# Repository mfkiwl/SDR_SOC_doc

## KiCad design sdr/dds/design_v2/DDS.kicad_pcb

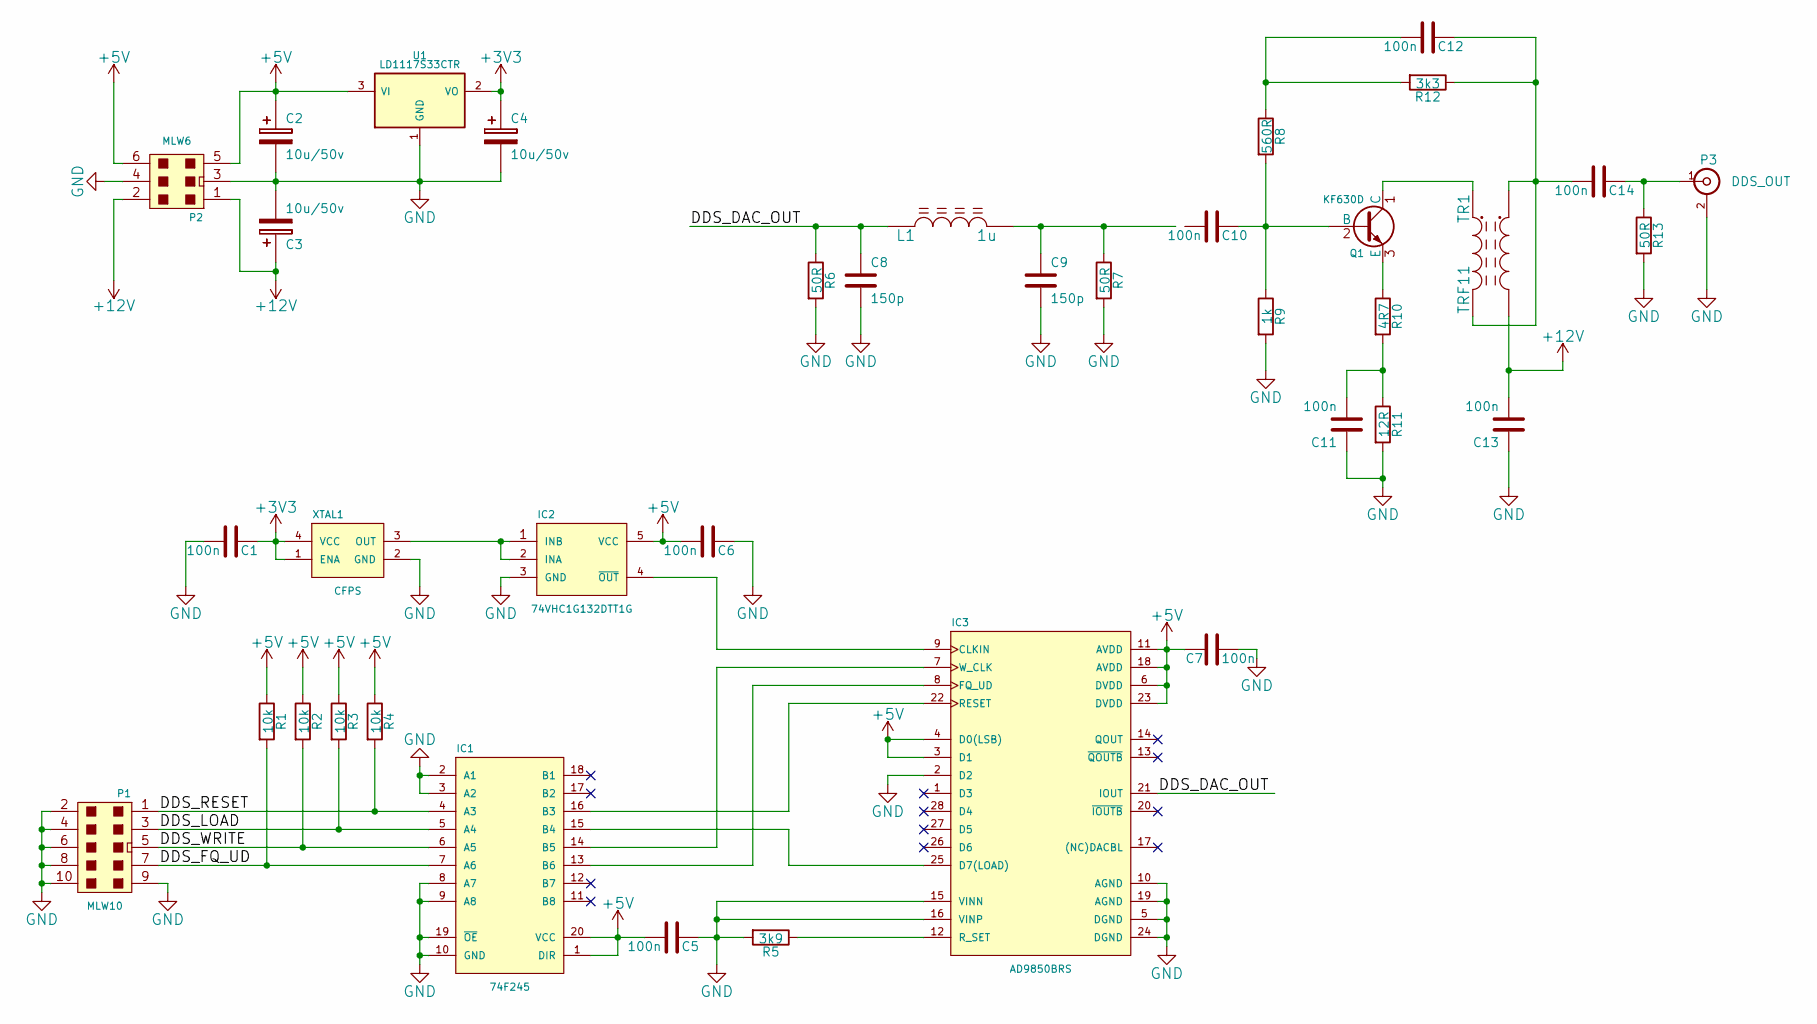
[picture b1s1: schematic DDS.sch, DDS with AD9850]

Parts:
C1, C5, C6, C7, C10, C11, C12, C13, C14: 100n; SMD-0805
C2, C3, C4: 10u/50v; Elko_vert_11.2x6.3mm_RM2.5
C8, C9: 150p; SMD-0805
IC1: 74F245; SO-20-L
IC2: 74VHC1G132DTT1G; SOT-23-5
IC3: AD9850BRS; SSOP-28_5.3x10.2mm_Pitch0.65mm
L1: 1u; R3-LARGE_PADS
P1: MLW10; vasch_strip_5x2_90
P2: MLW6; vasch_strip_3x2_90
P3: DDS_OUT; sma_90_r300.124.403
Q1: KF630D; OldSowjetaera_Transistor_Type-II_BigPads
R1, R2, R3, R4: 10k; R_1206
R5: 3k9; R_1206
R6, R7, R13: 50R; R_1206
R8: 560R; R_1206
R9: 1k; R_1206
R10: 4R7; R_1206
R11: 12R; R_1206
R12: 3k3; R_1206
TR1: TRF11; Transformer_Toroid_horizontal_Diameter12-5mm_Amidon-T44
U1: LD1117S33CTR; SOT-223
XTAL1: CFPS; SMD7x5

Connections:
+3V3: C1.1, C4.1, U1.2 (VO), U1.4, XTAL1.1 (ENA), XTAL1.4 (VCC)
+5V: C2.1, C5.2, C6.2, C7.2, IC1.1 (DIR), IC1.20 (VCC), IC2.5 (VCC), IC3.3 (D1), IC3.4 (D0(LSB)), IC3.6 (DVDD), IC3.11 (AVDD), IC3.18 (AVDD), IC3.23 (DVDD), P2.5, P2.6, R1.1, R2.1, R3.1, R4.1, U1.3 (VI)
+12V: C3.1, C13.2, P2.1, P2.2, TR1.4
/DDS_DAC_OUT: C8.1, IC3.21 (IOUT), L1.1, R6.1
/DDS_FQ_UD: IC1.7 (A6), P1.7, R1.2
/DDS_LOAD: IC1.5 (A4), P1.3, R3.2
/DDS_RESET: IC1.4 (A3), P1.1, R4.2
/DDS_WRITE: IC1.6 (A5), P1.5, R2.2
GND: C1.2, C2.2, C3.2, C4.2, C5.1, C6.1, C7.1, C8.2, C9.2, C11.1, C13.1, IC1.2 (A1), IC1.3 (A2), IC1.8 (A7), IC1.9 (A8), IC1.10 (GND), IC1.19 (~OE), IC2.3 (GND), IC3.2 (D2), IC3.5 (DGND), IC3.10 (AGND), IC3.15 (VINN), IC3.16 (VINP), IC3.19 (AGND), IC3.24 (DGND), P1.2, P1.4, P1.6, P1.8, P1.9, P1.10, P2.3, P2.4, P3.2 (Ext), R5.2, R6.2, R7.2, R9.2, R11.2, R13.2, U1.1 (GND), XTAL1.2 (GND)
unnamed: C10.1, Q1.2 (B), R8.2, R9.1
unnamed: C11.2, R10.2, R11.1
unnamed: C12.1, C14.2, R12.1, TR1.2, TR1.3
unnamed: C12.2, R8.1, R12.2
unnamed: C14.1, P3.1 (In), R13.1
unnamed: IC1.13 (B6), IC3.8 (FQ_UD)
unnamed: IC1.14 (B5), IC3.7 (W_CLK)
unnamed: IC1.15 (B4), IC3.25 (D7(LOAD))
unnamed: IC1.16 (B3), IC3.22 (RESET)
unnamed: IC2.1 (INB), IC2.2 (INA), XTAL1.3 (OUT)
unnamed: IC2.4 (~OUT), IC3.9 (CLKIN)
unnamed: IC3.12 (R_SET), R5.1
unnamed: Q1.1 (C), TR1.1
unnamed: Q1.3 (E), R10.1

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
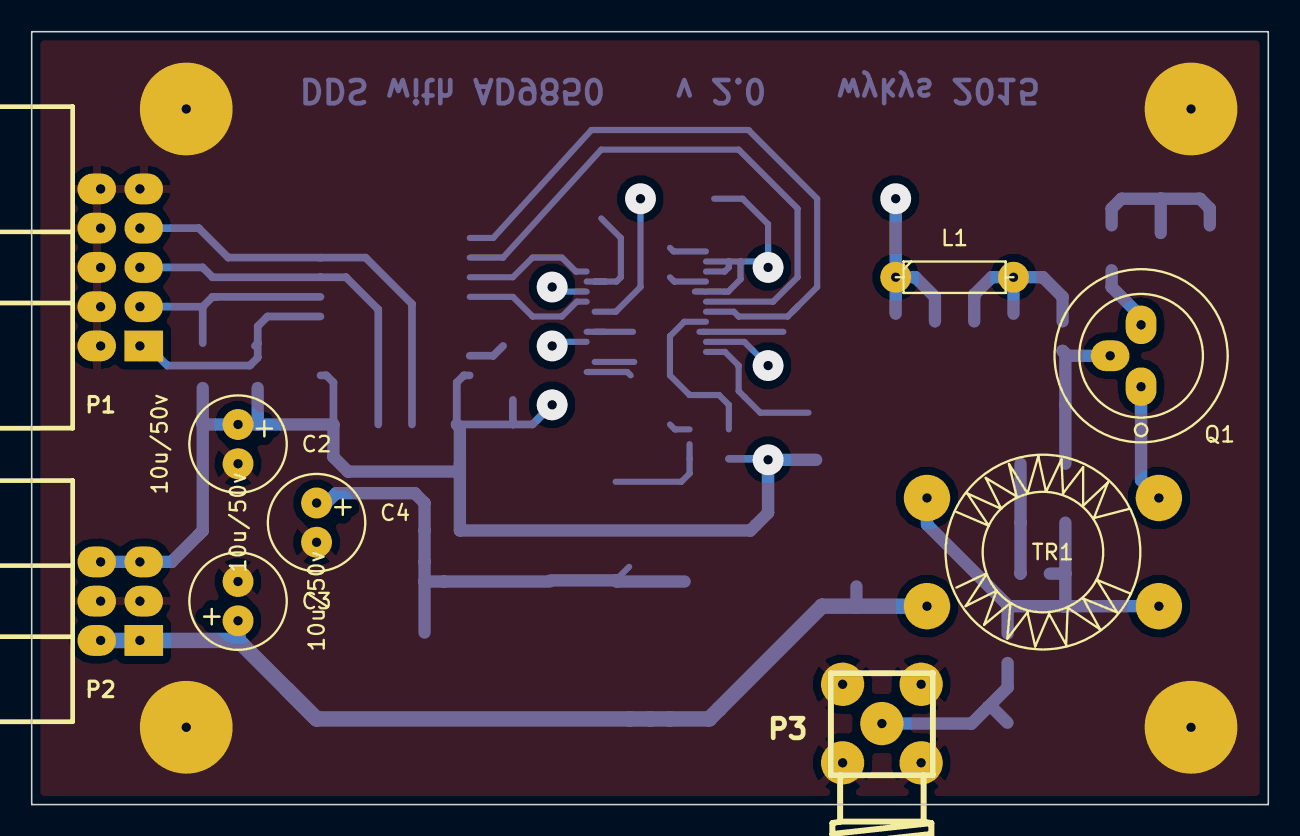
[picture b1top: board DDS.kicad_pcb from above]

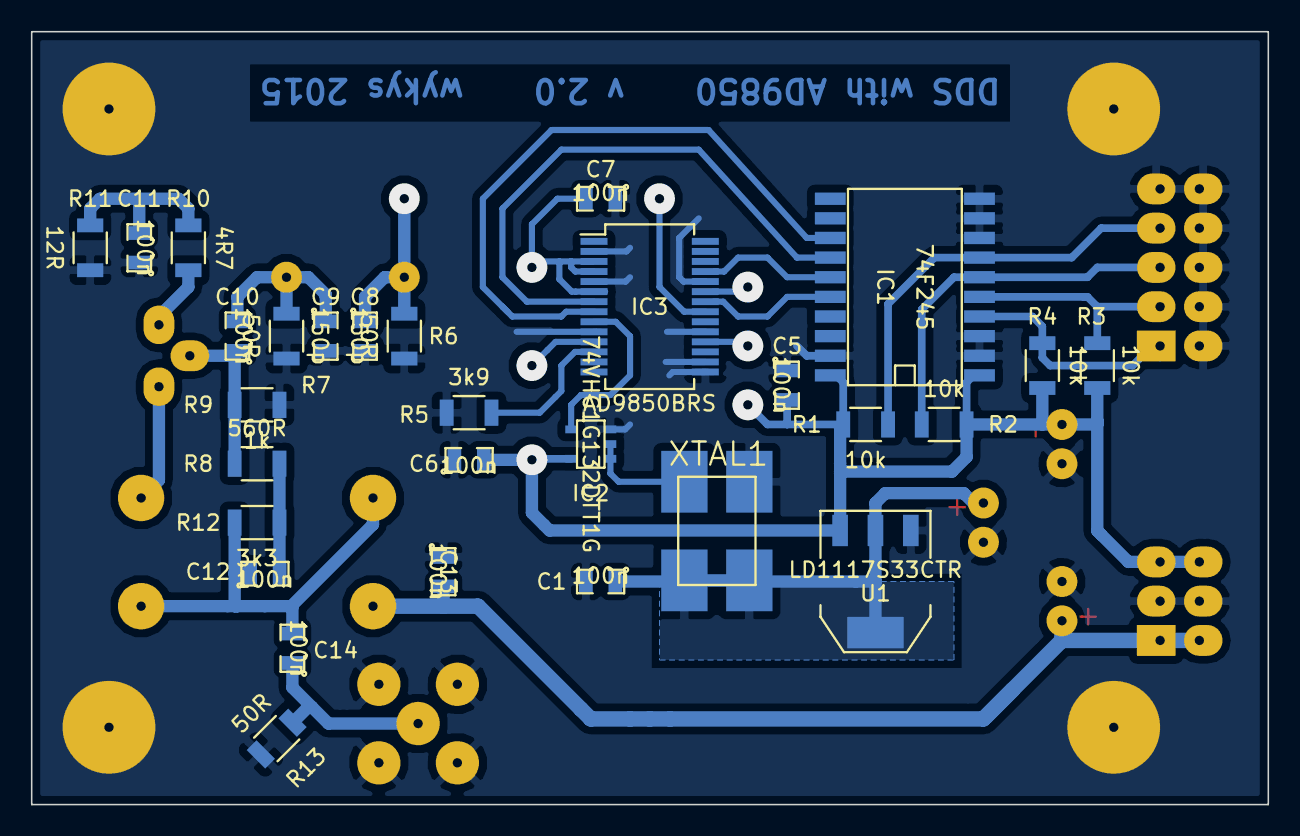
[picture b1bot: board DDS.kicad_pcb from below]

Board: 4 copper layers, 80.0 x 50.0 mm, 38 parts (29 on the bottom side), 24 nets.

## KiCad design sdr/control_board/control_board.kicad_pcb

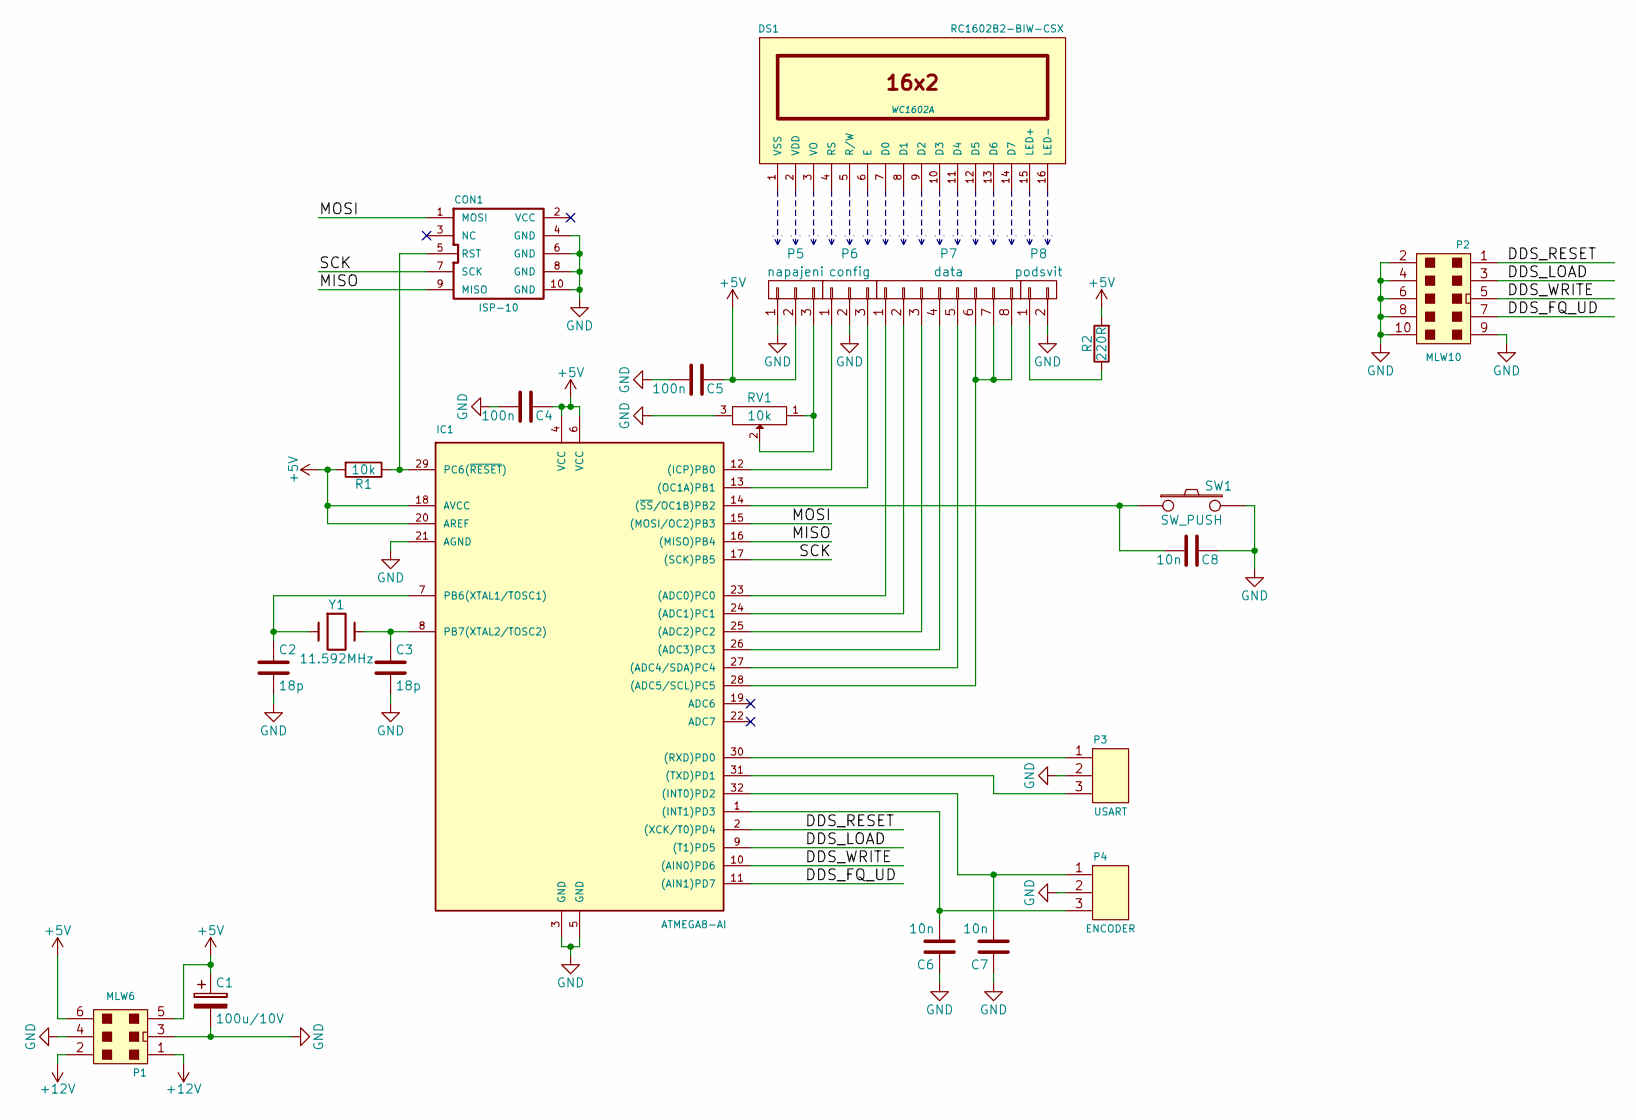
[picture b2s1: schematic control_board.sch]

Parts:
C1: 100u/10V; Elko_vert_11x5mm_RM2.5_CopperClear
C2, C3: 18p; C_0805
C4, C5: 100n; C_0805
C6, C7, C8: 10n; C_0805
CON1: ISP-10; vasch_strip_5x2
DS1: RC1602B2-BIW-CSX; WC1602A
IC1: ATMEGA8-AI; TQFP-32_7x7mm_Pitch0.8mm
P1: MLW6; vasch_strip_3x2_90
P2: MLW10; vasch_strip_5x2_90
P3: USART; MICROSWITCH_SPST
P4: ENCODER; MICROSWITCH_SPST
P5: napajeni; pin_socket_3
P6: config; pin_socket_3
P7: data; pin_socket_8
P8: podsvit; pin_socket_2
R1: 10k; R_1206
R2: 220R; Choke_Horizontal_RM15mm
RV1: 10k; Potentiometer_Trimmer-Suntan-TSR-3386P
SW1: SW_PUSH; Socket_MOLEX-KK-RM2-54mm_Lock_2pin_straight
Y1: 11.592MHz; Crystal_HC49-SD_SMD

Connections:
+5V: C1.1, C4.1, C5.1, IC1.4 (VCC), IC1.6 (VCC), IC1.18 (AVCC), IC1.20 (AREF), P1.5, P1.6, P5.2, R1.2, R2.2
+12V: P1.1, P1.2
/DDS_FQ_UD: IC1.11 ((AIN1)PD7), P2.7
/DDS_LOAD: IC1.9 ((T1)PD5), P2.3
/DDS_RESET: IC1.2 ((XCK/T0)PD4), P2.1
/DDS_WRITE: IC1.10 ((AIN0)PD6), P2.5
/MISO: CON1.9 (MISO), IC1.16 ((MISO)PB4)
/MOSI: CON1.1 (MOSI), IC1.15 ((MOSI/OC2)PB3)
/SCK: CON1.7 (SCK), IC1.17 ((SCK)PB5)
GND: C1.2, C2.2, C3.2, C4.2, C5.2, C6.1, C7.1, C8.1, CON1.4 (GND), CON1.6 (GND), CON1.8 (GND), CON1.10 (GND), IC1.3 (GND), IC1.5 (GND), IC1.21 (AGND), P1.3, P1.4, P2.2, P2.4, P2.6, P2.8, P2.9, P2.10, P3.2, P4.2, P5.1, P6.2, P8.2, RV1.3, SW1.2
unnamed: C2.1, IC1.7 (PB6(XTAL1/TOSC1)), Y1.1
unnamed: C3.1, IC1.8 (PB7(XTAL2/TOSC2)), Y1.2
unnamed: C6.2, IC1.1 ((INT1)PD3), P4.3
unnamed: C7.2, IC1.32 ((INT0)PD2), P4.1
unnamed: C8.2, IC1.14 ((~SS~/OC1B)PB2), SW1.1
unnamed: CON1.5 (RST), IC1.29 (PC6(~RESET~)), R1.1
unnamed: IC1.12 ((ICP)PB0), P6.1
unnamed: IC1.13 ((OC1A)PB1), P6.3
unnamed: IC1.23 ((ADC0)PC0), P7.1
unnamed: IC1.24 ((ADC1)PC1), P7.2
unnamed: IC1.25 ((ADC2)PC2), P7.3
unnamed: IC1.26 ((ADC3)PC3), P7.4
unnamed: IC1.27 ((ADC4/SDA)PC4), P7.5
unnamed: IC1.30 ((RXD)PD0), P3.1
unnamed: IC1.31 ((TXD)PD1), P3.3
unnamed: P5.3, RV1.1, RV1.2
unnamed: P8.1, R2.1

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
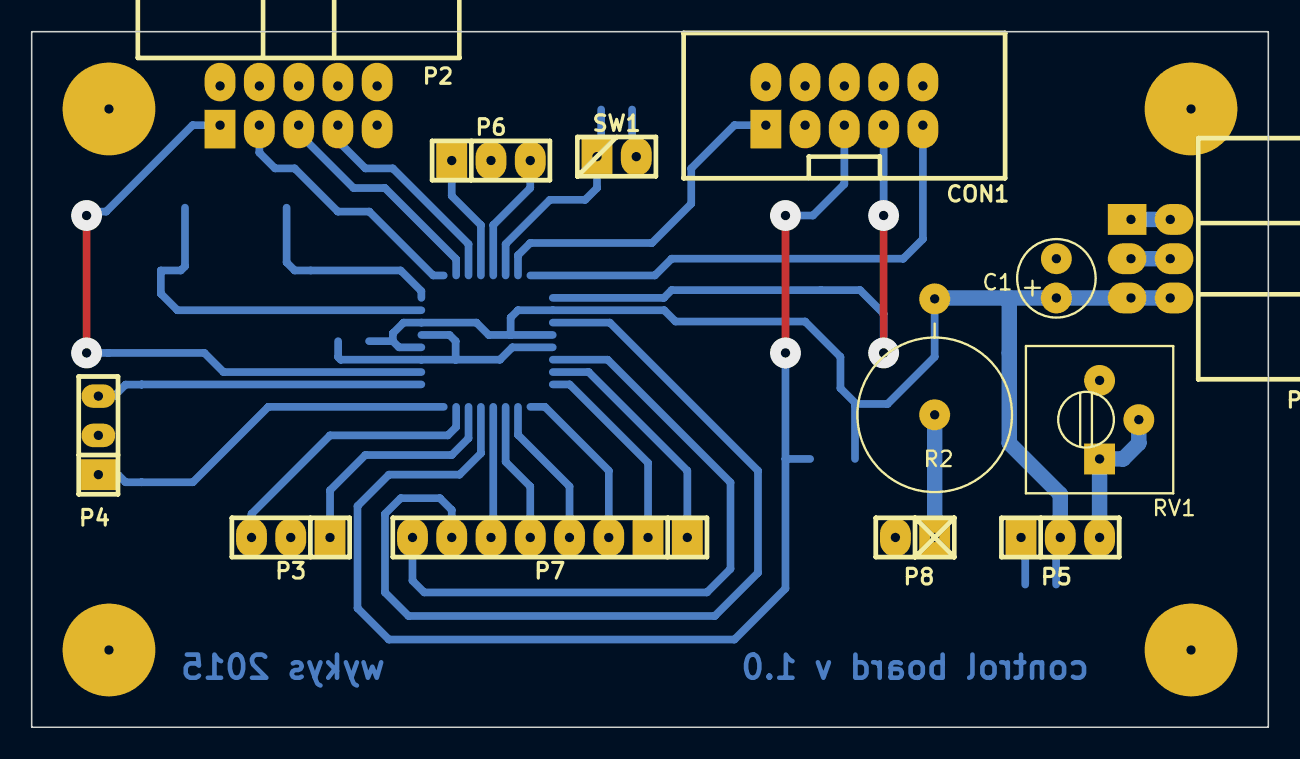
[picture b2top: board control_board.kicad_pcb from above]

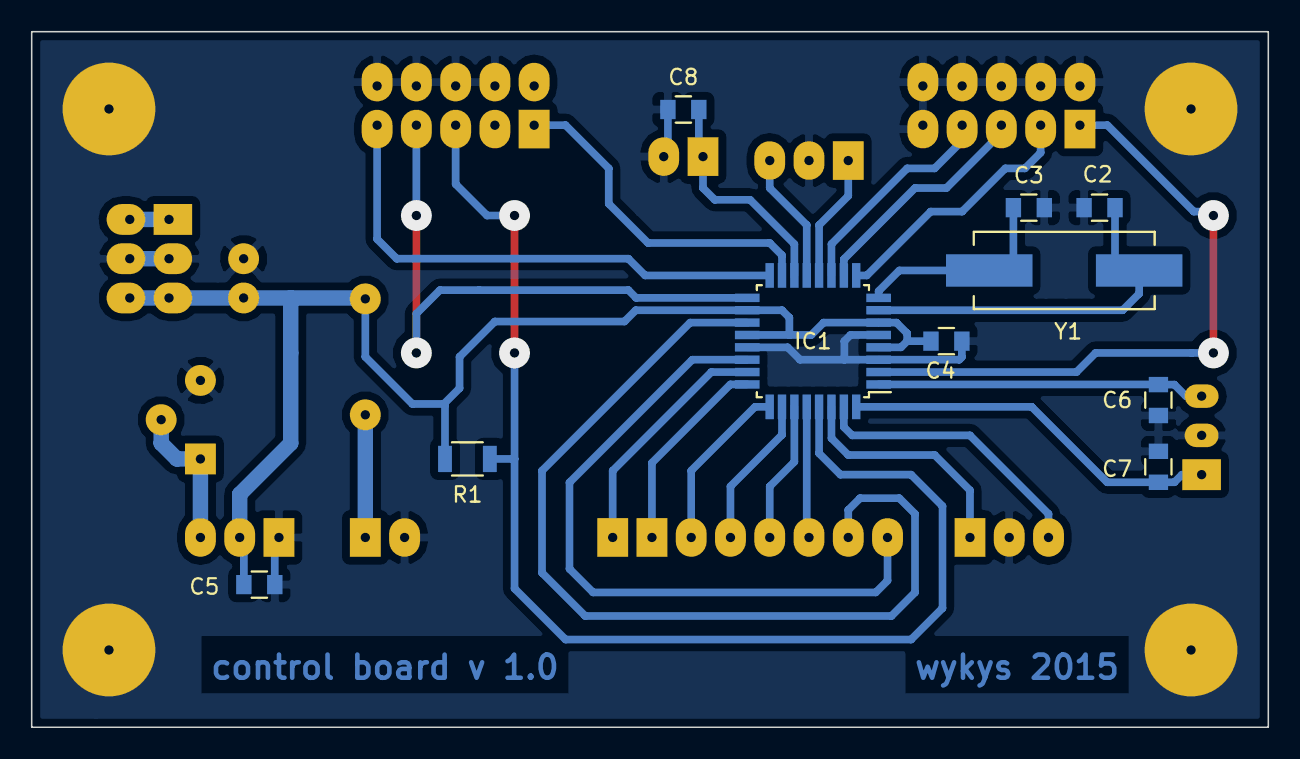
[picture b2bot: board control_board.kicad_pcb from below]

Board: 4 copper layers, 80.0 x 45.0 mm, 23 parts (10 on the bottom side), 30 nets.

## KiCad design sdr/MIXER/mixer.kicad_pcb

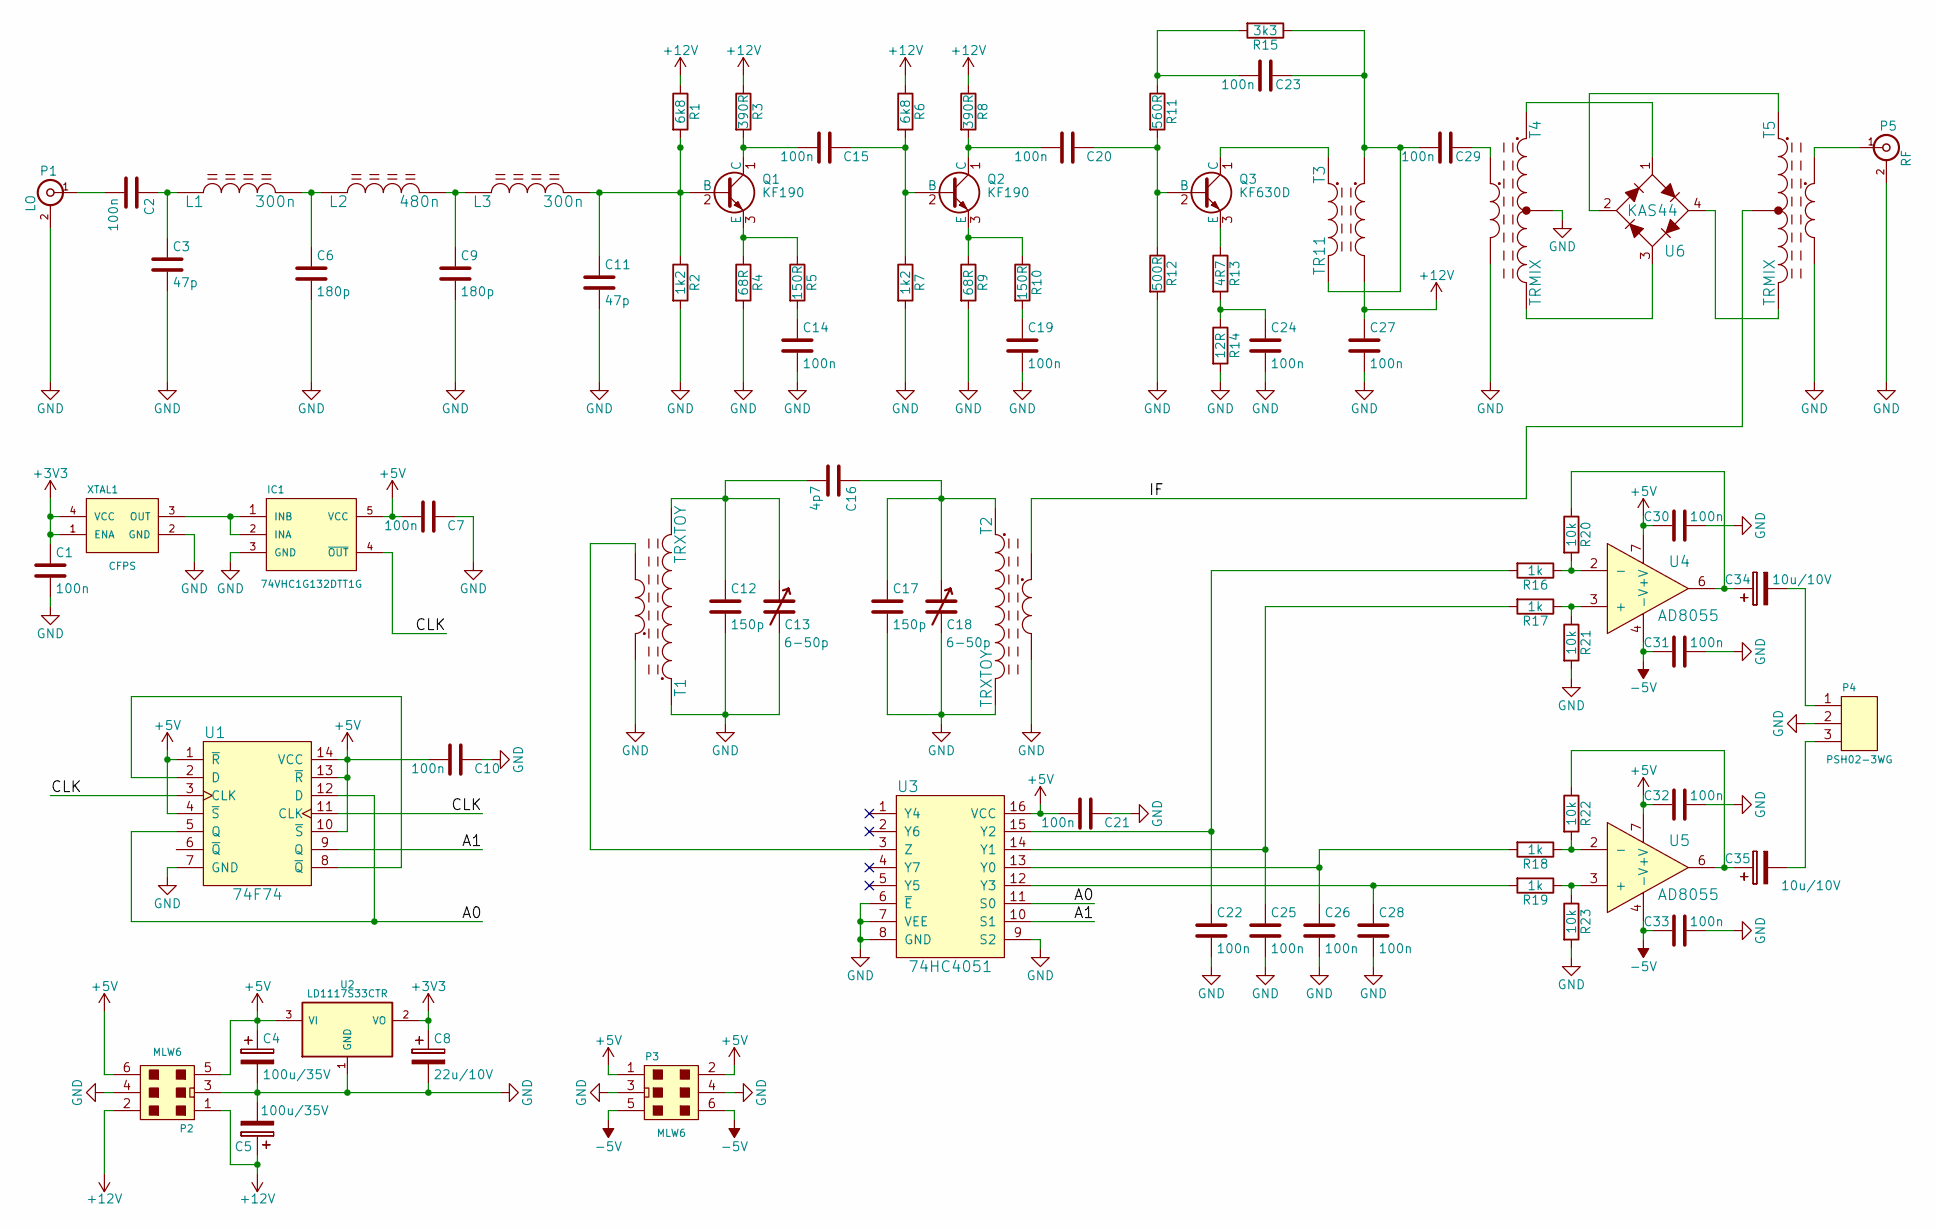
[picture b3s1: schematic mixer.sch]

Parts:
C1, C2, C7, C10, C14, C15, C19, C20, C21, C22, C23, C24, C25, C26, C27, C28, C29, C30, C31, C32, C33: 100n; C_0805
C3, C11: 47p; C_0805
C4, C5: 100u/35V; Elko_vert_11x5mm_RM2.5
C6, C9: 180p; C_0805
C8: 22u/10V; Elko_vert_11x5mm_RM2.5
C12, C17: 150p; C_0805
C13, C18: 6-50p; CT-6-50p
C16: 4p7; C_0805
C34, C35: 10u/10V; TantalC_SizeB_EIA-3528_Reflow
IC1: 74VHC1G132DTT1G; SOT-23-5
L1, L3: 300n; Choke_Toroid_8x16mm_Vertical
L2: 480n; Choke_Toroid_8x16mm_Vertical
P1: LO; sma_90_r300.124.403
P2, P3: MLW6; vasch_strip_3x2_90
P4: PSH02-3WG; Socket_Strip_Straight_1x03
P5: RF; sma_90_r300.124.403
Q1, Q2: KF190; TO-92_Inline_Narrow_Oval
Q3: KF630D; OldSowjetaera_Transistor_Type-II_BigPads
R1, R6: 6k8; R_1206
R2, R7: 1k2; R_1206
R3, R8: 390R; R_1206
R4, R9: 68R; R_1206
R5, R10: 150R; R_1206
R11: 560R; R_1206
R12: 500R; R_1206
R13: 4R7; R_1206
R14: 12R; R_1206
R15: 3k3; R_1206
R16, R17, R18, R19: 1k; R_1206
R20, R21, R22, R23: 10k; R_1206
T1, T2: TRXTOY; Transformer_Toroid_horizontal_Diameter12-5mm_Amidon-T44
T3: TR11; Transformer_Toroid_horizontal_Diameter12-5mm_Amidon-T44
T4, T5: TRMIX; Transformer_Toroid_Tapped_horizontal_Diameter12-5mm_Amidon-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
U1: 74F74; SOIC-14_3.9x8.7mm_Pitch1.27mm
U2: LD1117S33CTR; SOT-223
U3: 74HC4051; SO-16-N
U4, U5: AD8055; DIP-8__300_ELL
U6: KAS44; PowerMacro_PackageStyle-M234_NoHole_Housing
XTAL1: CFPS; SMD7x5

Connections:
+3V3: C1.1, C8.1, U2.2 (VO), U2.4, XTAL1.1 (ENA), XTAL1.4 (VCC)
+5V: C4.1, C7.2, C10.2, C21.2, C30.1, C32.1, IC1.5 (VCC), P2.5, P2.6, P3.1, P3.2, U1.1 (~R), U1.4 (~S), U1.10 (~S), U1.13 (~R), U1.14 (VCC), U2.3 (VI), U3.16 (VCC), U4.7 (+V), U5.7 (+V)
+12V: C5.1, C27.1, P2.1, P2.2, R1.1, R3.1, R6.1, R8.1, T3.4
-5V: C31.1, C33.1, P3.5, P3.6, U4.4 (-V), U5.4 (-V)
/A0: U1.5 (Q), U1.12 (D), U3.11 (S0)
/A1: U1.9 (Q), U3.10 (S1)
/CLK: IC1.4 (~OUT), U1.3 (CLK), U1.11 (CLK)
/IF: T2.3, T5.2
GND: C1.2, C3.2, C4.2, C5.2, C6.2, C7.1, C8.2, C9.2, C10.1, C11.2, C12.2, C13.2, C14.2, C17.2, C18.2, C19.2, C21.1, C22.2, C24.2, C25.2, C26.2, C27.2, C28.2, C30.2, C31.2, C32.2, C33.2, IC1.3 (GND), P1.2 (Ext), P2.3, P2.4, P3.3, P3.4, P4.2, P5.2 (Ext), R2.2, R4.2, R7.2, R9.2, R12.2, R14.2, R21.2, R23.2, T1.1, T1.3, T2.2, T2.4, T4.2, T4.5, T5.5, U1.7 (GND), U2.1 (GND), U3.6 (~E), U3.7 (VEE), U3.8 (GND), U3.9 (S2), XTAL1.2 (GND)
unnamed: C2.1, C3.1, L1.1
unnamed: C2.2, P1.1 (In)
unnamed: C6.1, L1.2, L2.1
unnamed: C9.1, L2.2, L3.1
unnamed: C11.1, L3.2, Q1.2 (B), R1.2, R2.1
unnamed: C12.1, C13.1, C16.2, T1.2
unnamed: C14.1, R5.2
unnamed: C15.1, Q2.2 (B), R6.2, R7.1
unnamed: C15.2, Q1.1 (C), R3.2
unnamed: C16.1, C17.1, C18.1, T2.1
unnamed: C19.1, R10.2
unnamed: C20.1, Q3.2 (B), R11.2, R12.1
unnamed: C20.2, Q2.1 (C), R8.2
unnamed: C22.1, R16.2, U3.15 (Y2)
unnamed: C23.1, C29.2, R15.1, T3.2, T3.3
unnamed: C23.2, R11.1, R15.2
unnamed: C24.1, R13.2, R14.1
unnamed: C25.1, R17.2, U3.14 (Y1)
unnamed: C26.1, R18.2, U3.13 (Y0)
unnamed: C28.1, R19.2, U3.12 (Y3)
unnamed: C29.1, T4.4
unnamed: C34.1, R20.1, U4.6
unnamed: C34.2, P4.1
unnamed: C35.1, R22.1, U5.6
unnamed: C35.2, P4.3
unnamed: IC1.1 (INB), IC1.2 (INA), XTAL1.3 (OUT)
unnamed: P5.1 (In), T5.4
unnamed: Q1.3 (E), R4.1, R5.1
unnamed: Q2.3 (E), R9.1, R10.1
unnamed: Q3.1 (C), T3.1
unnamed: Q3.3 (E), R13.1
unnamed: R16.1, R20.2, U4.2 (-)
unnamed: R17.1, R21.1, U4.3 (+)
unnamed: R18.1, R22.2, U5.2 (-)
unnamed: R19.1, R23.1, U5.3 (+)
unnamed: T1.4, U3.3 (Z)
unnamed: T4.1, U6.1
unnamed: T4.3, U6.3
unnamed: T5.1, U6.2
unnamed: T5.3, U6.4
unnamed: U1.2 (D), U1.8 (~Q)

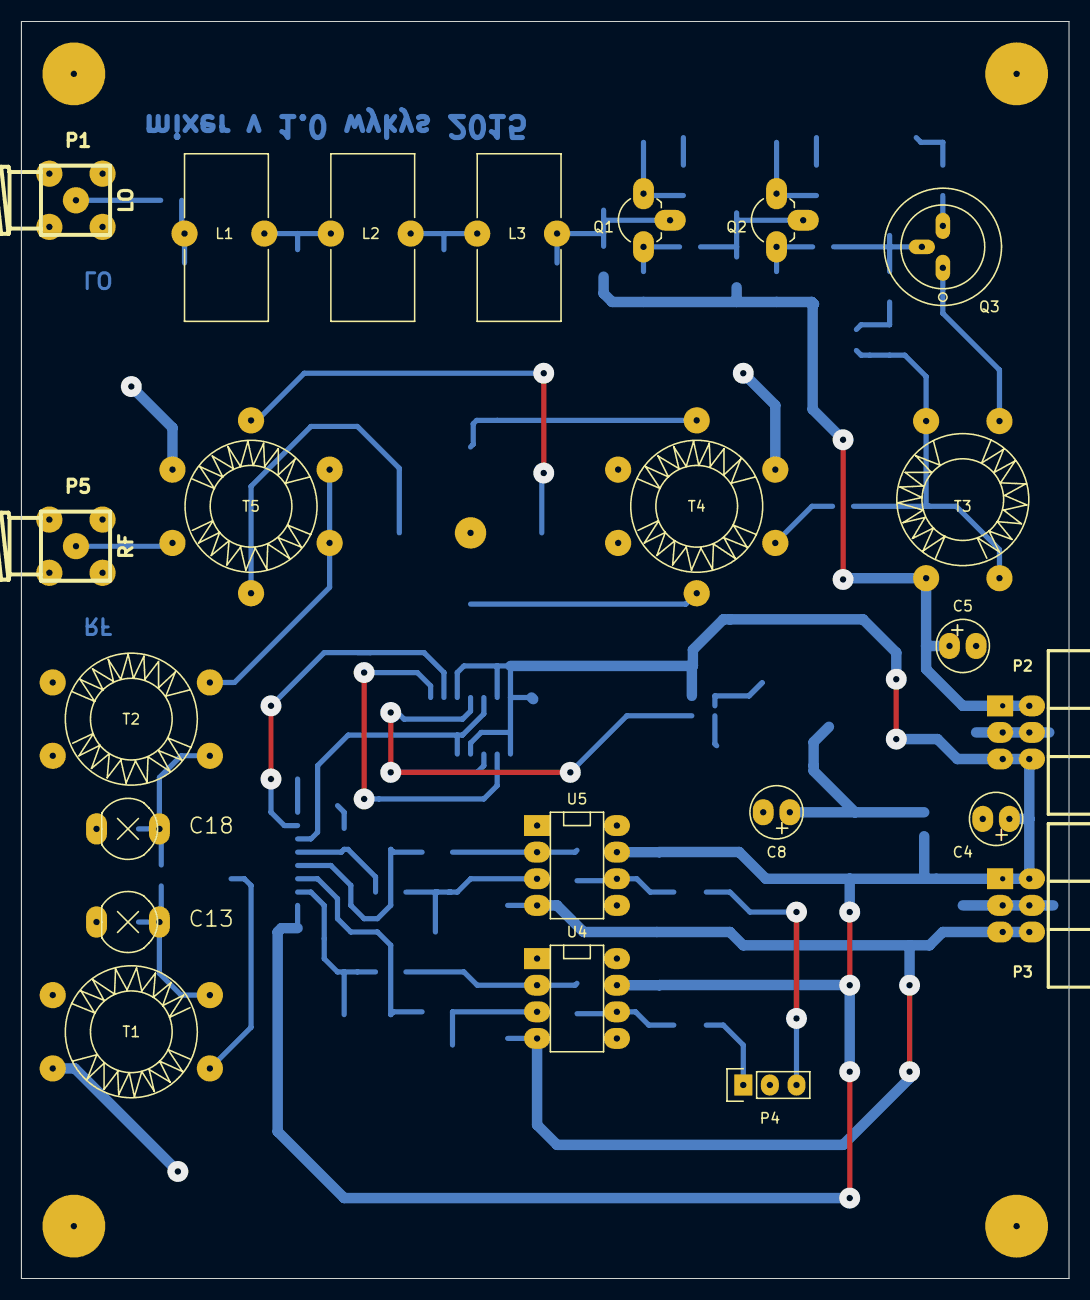
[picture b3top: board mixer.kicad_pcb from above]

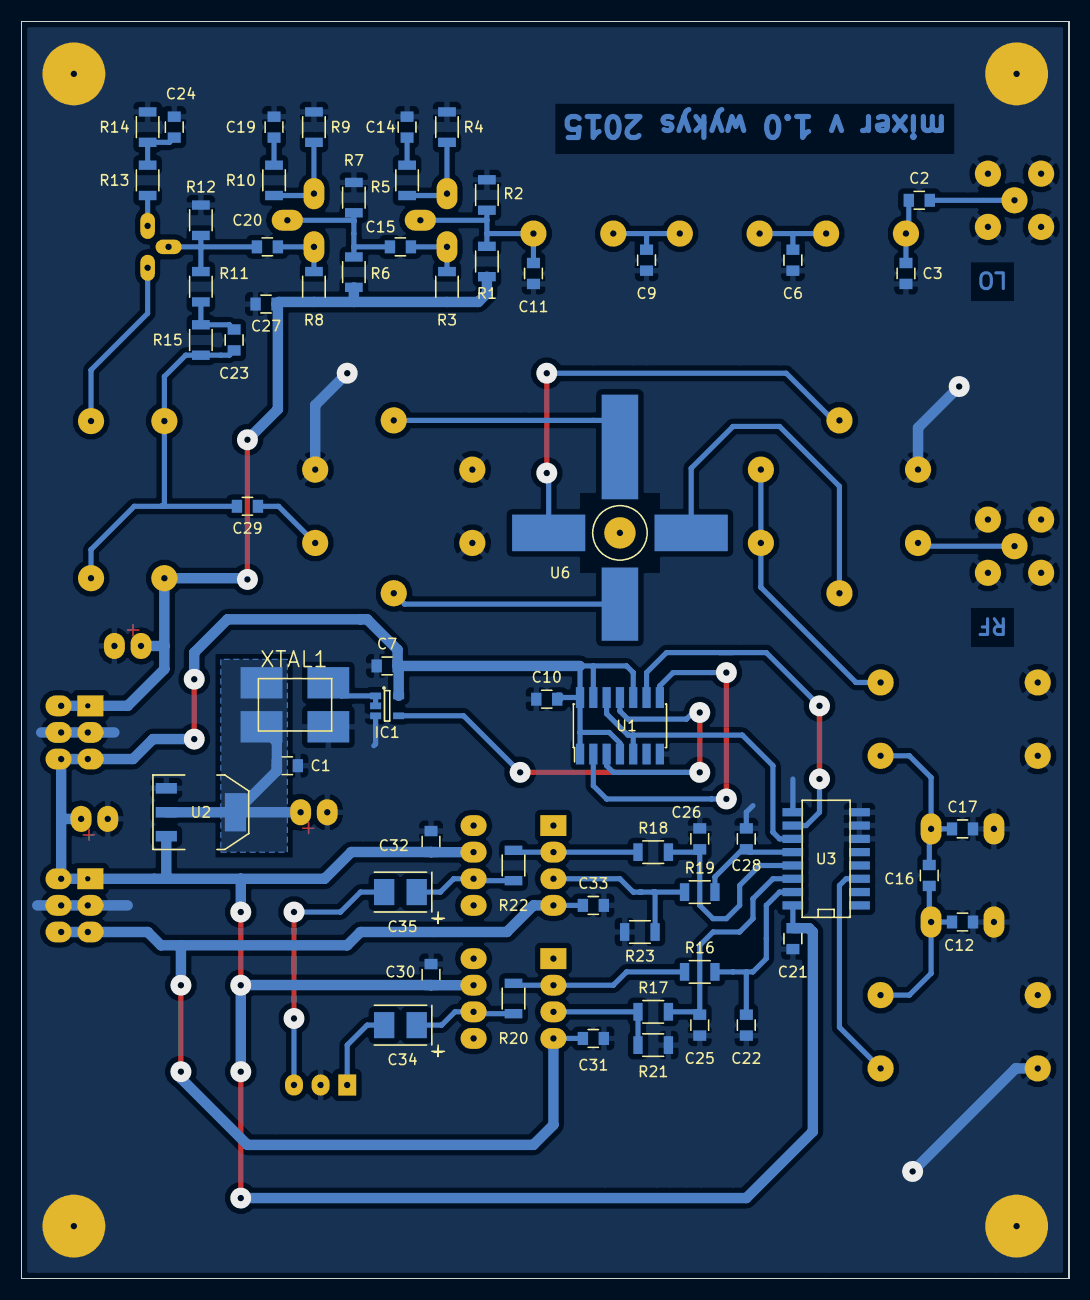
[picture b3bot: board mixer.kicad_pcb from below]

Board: 2 copper layers, 100.0 x 120.0 mm, 82 parts (59 on the bottom side), 50 nets.

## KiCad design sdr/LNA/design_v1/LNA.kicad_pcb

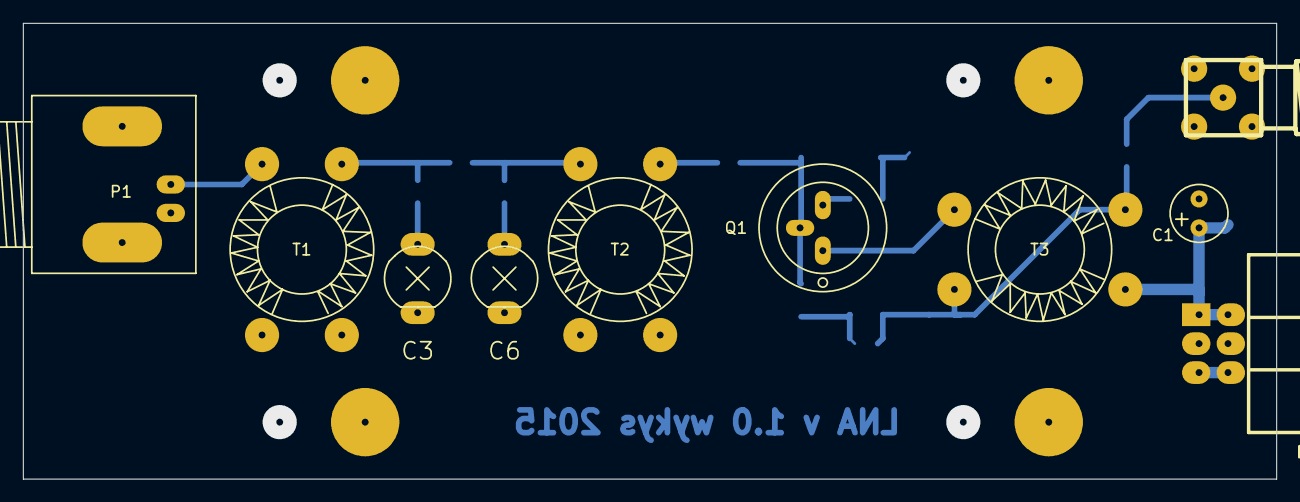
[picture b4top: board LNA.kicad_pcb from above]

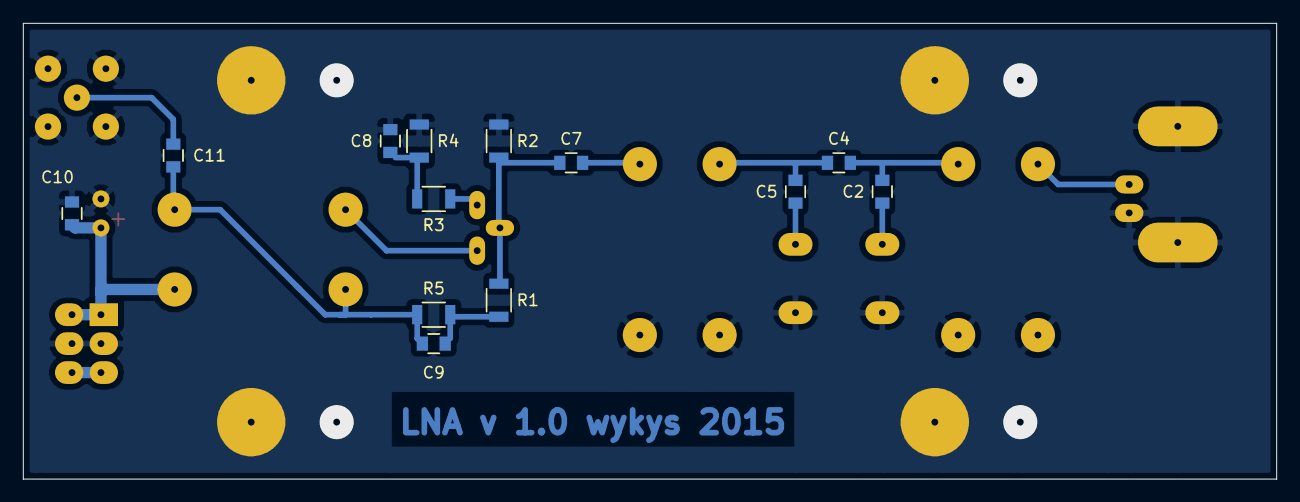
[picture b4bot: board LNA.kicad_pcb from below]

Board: 2 copper layers, 110.0 x 40.0 mm, 23 parts (13 on the bottom side), 16 nets.

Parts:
C1: 10u/50v; Elko_vert_11x5mm_RM2.5
C2, C5: 100p; C_0805
C3, C6: 6-50p; CT-6-50p
C4: 4p7; C_0805
C7, C8, C9, C10, C11: 100n; C_0805
P1: ANT; BNC_Socket_TYCO-AMP_LargePads
P2: MLW6; vasch_strip_3x2_90
P3: LNA_OUT; sma_90_r300.124.403
Q1: KF630D; OldSowjetaera_Transistor_Type-II_BigPads
R1: 560R; R_1206
R2: 500R; R_1206
R3: 4R7; R_1206
R4: 12R; R_1206
R5: 3k3; R_1206
T1, T2: TRXTOY; Transformer_Toroid_horizontal_Diameter12-5mm_Amidon-T44
T3: TR11; Transformer_Toroid_horizontal_Diameter12-5mm_Amidon-T44

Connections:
+5V: P2.5, P2.6
+12V: C1.1, C10.2, P2.1, P2.2, T3.4
GND: C1.2, C3.2, C6.2, C8.1, C10.1, P1.2, P2.3, P2.4, P3.2, R2.2, R4.2, T1.2, T1.4, T2.2, T2.4
unnamed: C2.1, C4.2, T1.1
unnamed: C2.2, C3.1
unnamed: C4.1, C5.1, T2.1
unnamed: C5.2, C6.1
unnamed: C7.1, Q1.2, R1.2, R2.1
unnamed: C7.2, T2.3
unnamed: C8.2, R3.2, R4.1
unnamed: C9.2, R1.1, R5.2
unnamed: C11.1, P3.1
unnamed: C9.1, C11.2, R5.1, T3.2, T3.3
unnamed: P1.1, T1.3
unnamed: Q1.1, T3.1
unnamed: Q1.3, R3.1
